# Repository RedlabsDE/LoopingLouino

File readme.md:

# LoopingLouino Project

find pictures and further description here: https://redlabs.de/blog/looping-louino/

## Repository Overview
- **documentation**
  - pictures of this project
- **firmware**
  - Arduino Project
- **hardware**
  - **KiCAD** Project Folder including schematic, PCB layout and BOM
  - **schematic** and fabrication layer drawing as PDF
  - **datasheet** of used components
  
## Hardware
- Order PCB: https://aisler.net/p/MKIYMUSK
- Assemble PCB (find BOM in \hardware\schematic)
- Rework PCB as described in the schematic

## Firmware

### Flash Arduino bootloader to your Atmega328

1. Open Atmel Studio (now Microchip Studio)
2. Start the Tool Manager. Connec your Atmel ISP to your PC and to the PCB (CON2, ISP 6-pin).
3. Select Tool and Device. Apply & Read.
4. "Fuses": Set Fuses (according to picture "Arduino Fuses.pg"). Program fuses to Device.
5. "Memories": For Flash, select the "optiboot_atmega328.hex" file. Program&Verify.

... find pictures and data here: \firmware\Arduino Bootloader

### Upload the LoopingLouino Fimrware 

Prepare:
- Get an USB/UART converter
- Connect the UART to the PCB (Pinheader P1, or use the Audio Jack J1)

Upload:
1. Open the firmware folder in VSCode
2. Install the "PlatformIO IDE" extension
3. Open the folder "180223-094129-pro16MHzatmega328" with the extension
4. Build and Upload the project.

... find other projects: https://redlabs.de/

### Debug the Firmware

In main.cpp set "#define DEBUG 1" to get serial debug information (8n1 19200)

### Adaptions in the Firware

According to the used Supply Voltage, set: #define SPEED_CORRECTION_FACTOR (main.h)

According to the number of LEDs used, set: #define NUM_LEDS (LEDcntrl.h)

## Mechanics

//TODO: add pictures

Open all screws (short / long)

remove black cable (between motor and batteries)
remove red cable (between switch and batteries)
remove battery clips

add new black cable to motor (20cm)
add new red cable to switch (20cm)

cut through plastic (battery holder)
drill through plastic frame (for DC Jack, Button and optional RC-Jack)

cut digital LED strip and attach 3-wire ribbon cable (20LEDs, or other number)

solder 3-wire LED cable to PCB
solder 2-Wire Motor-and-Switch cable to PCB

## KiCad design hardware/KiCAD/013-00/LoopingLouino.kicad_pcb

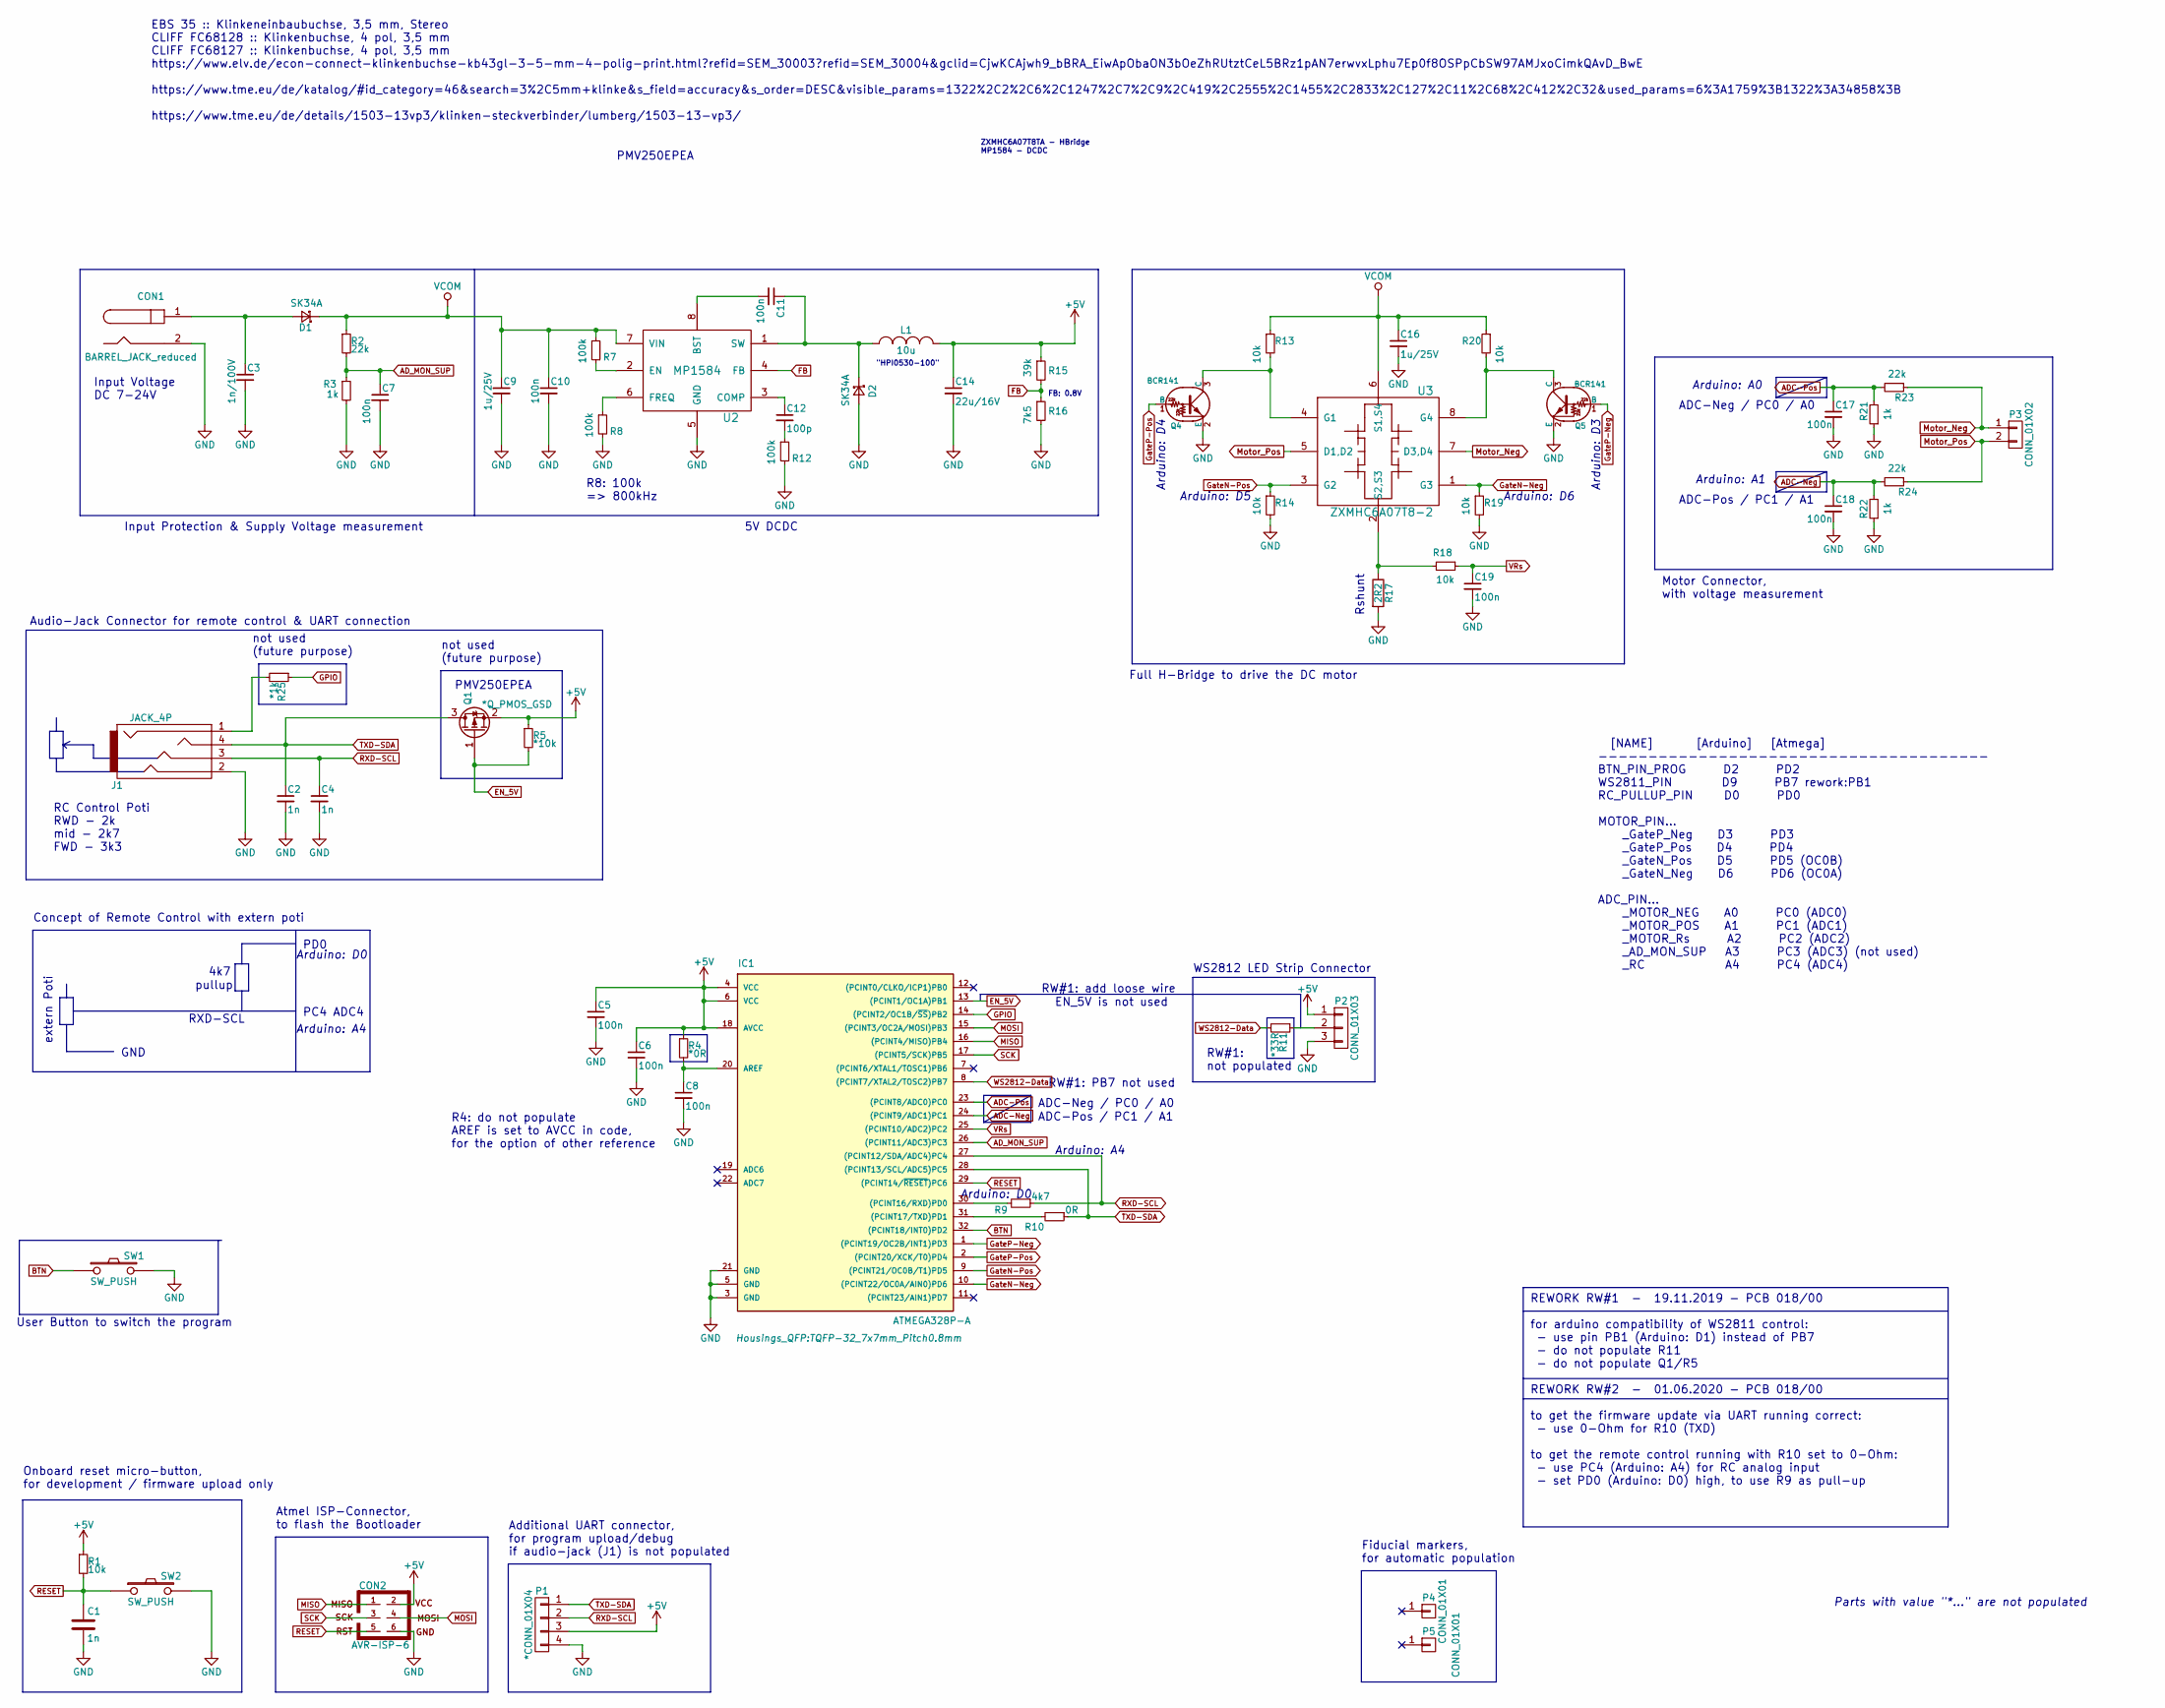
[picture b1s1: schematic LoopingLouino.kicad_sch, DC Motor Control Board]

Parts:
C1, C2, C4: 1n; C_0603
C3: 1n/100V; C_0603
C5, C6, C7, C8, C10, C11, C17, C18, C19: 100n; C_0603
C9, C16: 1u/25V; C_0805
C12: 100p; C_0603
C14: 22u/16V; C_1206
CON1: BARREL_JACK_reduced
CON2: AVR-ISP-6; MicroMatch_2x3_SMD
D1, D2: SK34A; D_SMA
IC1: ATMEGA328P-A; TQFP-32_7x7mm_Pitch0.8mm
J1: JACK_4P; Klinkenbuchse-1503-13VP3
L1: 10u; Inductor_HPI0530-xxx
P1: *CONN_01X04; PIN_ARRAY_4x1_drill_0.8mm
P2: CONN_01X03; PIN_ARRAY_3x1_drill_0.8mm
P3: CONN_01X02; JST_XH2P_oval_pads
P4, P5: CONN_01X01; Fiducial_1mm_Dia_2mm_Outer
Q1: *Q_PMOS_GSD; SOT-23-RL
Q4, Q5: BCR141; SOT-23-RL
R1, R13, R14, R18, R19, R20: 10k; R_0603
R2, R23, R24: 22k; R_0603
R3, R21, R22: 1k; R_0603
R4: *0R; R_0603
R5: *10k; R_0603
R7, R8, R12: 100k; R_0603
R9: 4k7; R_0603
R10: 0R; R_0603
R11: *33R; R_0603
R15: 39k; R_0603
R16: 7k5; R_0603
R17: 2R2; R_0805_redlabs
R25: *1k; R_0603
SW1: SW_PUSH; SW_Tactile_SPST_Angled_PTS645Vx83-2LFS
SW2: SW_PUSH; SMD_pushbutton_4x6mm
U2: MP1584; SO8N-RL
U3: ZXMHC6A07T8-2; SOT-223-8

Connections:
+5V: C5.1, C6.1, C14.1, CON2.2, IC1.4 (VCC), IC1.6 (VCC), IC1.18 (AVCC), L1.2, P1.3, P2.1, Q1.2 (S), R1.1, R4.1, R5.1, R15.1
ADC-Neg: C18.1, IC1.24 ((PCINT9/ADC1)PC1), R22.2, R24.2
ADC-Pos: C17.1, IC1.23 ((PCINT8/ADC0)PC0), R21.2, R23.2
AD_MON_SUP: C7.1, IC1.26 ((PCINT11/ADC3)PC3), R2.2, R3.1
BTN: IC1.32 ((PCINT18/INT0)PD2), SW1.1
EN_5V: IC1.13 ((PCINT1/OC1A)PB1), Q1.1 (G), R5.2
FB: R15.2, R16.1, U2.4 (FB)
GND: C1.2, C2.2, C3.2, C4.2, C5.2, C6.2, C7.2, C8.2, C9.2, C10.2, C14.2, C16.2, C17.2, C18.2, C19.2, CON1.2, CON2.6, D2.2 (A), IC1.3 (GND), IC1.5 (GND), IC1.21 (GND), J1.2, P1.4, P2.3, Q4.2 (E), Q5.2 (E), R3.2, R8.2, R12.2, R14.2, R16.2, R17.2, R19.2, R21.1, R22.1, SW1.2, SW2.2, U2.5 (GND)
GPIO: IC1.14 ((PCINT2/OC1B/~SS)PB2), R25.1
GateN-Neg: IC1.10 ((PCINT22/OC0A/AIN0)PD6), R19.1, U3.1 (G3)
GateN-Pos: IC1.9 ((PCINT21/OC0B/T1)PD5), R14.1, U3.3 (G2)
GateP-Neg: IC1.1 ((PCINT19/OC2B/INT1)PD3), Q5.1 (B)
GateP-Pos: IC1.2 ((PCINT20/XCK/T0)PD4), Q4.1 (B)
MISO: CON2.1, IC1.16 ((PCINT4/MISO)PB4)
MOSI: CON2.4, IC1.15 ((PCINT3/OC2A/MOSI)PB3)
Motor_Neg: P3.1, R23.1, U3.7 (D3,D4)
Motor_Pos: P3.2, R24.1, U3.5 (D1,D2)
unnamed: C3.1, CON1.1, D1.2 (A)
unnamed: C8.1, IC1.20 (AREF), R4.2
unnamed: C11.1, D2.1 (K), L1.1, U2.1 (SW)
unnamed: C11.2, U2.8 (BST)
unnamed: C12.1, U2.3 (COMP)
unnamed: C12.2, R12.1
unnamed: IC1.30 ((PCINT16/RXD)PD0), R9.2
unnamed: IC1.31 ((PCINT17/TXD)PD1), R10.2
unnamed: J1.1, R25.2
unnamed: P2.2, R11.1
unnamed: Q4.3 (C), R13.2, U3.4 (G1)
unnamed: Q5.3 (C), R20.2, U3.8 (G4)
unnamed: R7.2, U2.2 (EN)
unnamed: R8.1, U2.6 (FREQ)
unnamed: R17.1, R18.2, U3.2 (S2,S3)
RESET: C1.1, CON2.5, IC1.29 ((PCINT14/~RESET)PC6), R1.2, SW2.1
RXD-SCL: C4.1, IC1.27 ((PCINT12/SDA/ADC4)PC4), J1.3, P1.2, R9.1
SCK: CON2.3, IC1.17 ((PCINT5/SCK)PB5)
TXD-SDA: C2.1, IC1.28 ((PCINT13/SCL/ADC5)PC5), J1.4, P1.1, Q1.3 (D), R10.1
VCOM: C9.1, C10.1, C16.1, D1.1 (K), R2.1, R7.1, R13.1, R20.1, U2.7 (VIN), U3.6 (S1,S4)
VRs: C19.1, IC1.25 ((PCINT10/ADC2)PC2), R18.1
WS2812-Data: IC1.8 ((PCINT7/XTAL2/TOSC2)PB7), R11.2

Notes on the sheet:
PMV250EPEA
Arduino: D6
ADC-Pos / PC1 / A1
ADC-Neg / PC0 / A0
R4: do not populate AREF is set to AVCC in code, for the option of other reference
Motor Connector, with voltage measurement
Parts with value "*..." are not populated
Arduino: D4
GND
Arduino: D0
Additional UART connector, for program upload/debug if audio-jack (J1) is not populated
"HPI0530-100"
RW#1: PB7 not used
User Button to switch the program
Rshunt
Onboard reset micro-button, for development / firmware upload only
Input Protection & Supply Voltage measurement
Atmel ISP-Connector, to flash the Bootloader
FB: 0.8V
REWORK RW#1 - 19.11.2019 - PCB 018/00 for arduino compatibility of WS2811 control: - use pin PB1 (Arduino: D1) instead of PB7 - do not populate R11 - do not populate Q1/R5 REWORK RW#2 - 01.06.2020 - PCB 018/00 to get the firmware update via UART running correct: - use 0-Ohm for R10 (TXD) to get the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
WS2812 LED Strip Connector
pullup
Arduino: A4
RC Control Poti RWD - 2k mid - 2k7 FWD - 3k3
EBS 35 :: Klinkeneinbaubuchse, 3,5 mm, Stereo CLIFF FC68128 :: Klinkenbuchse, 4 pol, 3,5 mm CLIFF FC68127 :: Klinkenbuchse, 4 pol, 3,5 mm https://www.elv.de/econ-connect-klinkenbuchse-kb43gl-3-5-mm-4-polig-print.html?refid=SEM_30003?refid=SEM_30004&gclid=CjwKCAjwh9_bBRA_EiwApObaON3bOeZhRUtztCeL5BRz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
not used (future purpose)
4k7
RW#1: not populated
Audio-Jack Connector for remote control & UART connection
RXD-SCL
[NAME] [Arduino] [Atmega] --------------------------------------- BTN_PIN_PROG D2 PD2 WS2811_PIN D9 PB7 rework:PB1 RC_PULLUP_PIN D0 PD0 MOTOR_PIN... _GateP_Neg D3 PD3 _GateP_Pos D4 PD4 _GateN_Pos D5 PD5 (OC0B) _GateN_Neg D6 PD6 (OC0A) ADC_PIN... _MOTOR_NEG A0 PC0 (ADC0) _MOTOR_POS A1 PC1 (ADC1) _MO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
EN_5V is not used
Arduino: D3
Arduino: D5
R8: 100k => 800kHz
Arduino: A0
Full H-Bridge to drive the DC motor
extern Poti
RW#1: add loose wire
Fiducial markers, for automatic population

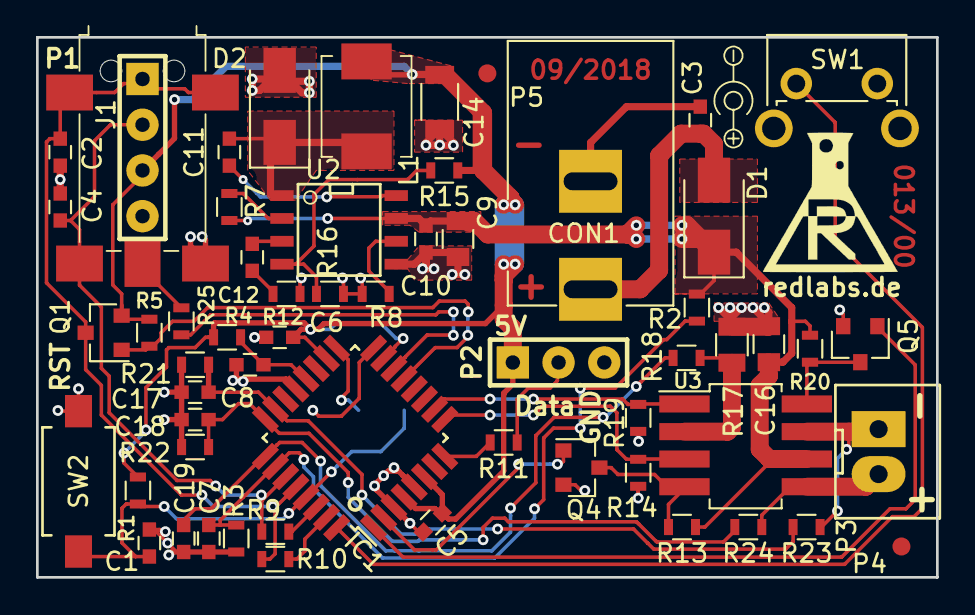
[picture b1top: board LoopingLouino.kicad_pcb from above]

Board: 2 copper layers, 50.0 x 30.0 mm, 60 parts (1 on the bottom side), 39 nets.

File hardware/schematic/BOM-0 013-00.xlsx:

redlabs.de | BOM 013/00 | LoopingLouino
 |  | Total parts: | 50
v C | 22u | C_1206 | 1
C14 | 22u
v C | 100p | C_0603 | 1
C12 | 100p
v C | 1n | C_0603 | 4
C1 | 1n
C2 | 1n
C3 | 1n/200V
C4 | 1n
v C | 100n | C_0603 | 9
C5 | 100n
C6 | 100n
C7 | 100n
C8 | 100n
C10 | 100n/25V
C11 | 100n
C17 | 100n
C18 | 100n
C19 | 100n
v C | 1u/25V | C_0805 | 2
C9 | 1u/25V
C16 | 1u/25V
v R | 2R2 | R_0805 | 1
R17 | 2R2
v R | 0R | R_0603 | 1
R10 | 0R
v R | 1k | R_0603 | 3
R3 | 1k
R21 | 1k
R22 | 1k
v R | 4k7 | R_0603 | 1
R9 | 4k7
v R | 7k5 | R_0603 | 1
R16 | 7k5
v R | 10k | R_0603 | 6
R1 | 10k
R13 | 10k
R14 | 10k
R18 | 10k
R19 | 10k
R20 | 10k
v R | 22k | R_0603 | 3
R2 | 22k
R23 | 22k
R24 | 22k
v R | 39k | R_0603 | 1
R15 | 39k
v R | 100k | R_0603 | 3
R7 | 100k
R8 | 100k
R12 | 100k
v D | SK34A | D_SMA | 2
D1 | SK34A
D2 | SK34A
v L | 10uH | D_SMA | 1
L1 | 10uH (HPI0530-100)
v Q | BCR141 | SOT-23 | 2
Q4 | BCR141
Q5 | BCR141
v IC |  |  | 3
IC1 | ATMEGA328P-A | TQFP-32_7x7mm_Pitch0.8mm
U2 | MP1584 | SO8N
U3 | ZXMHC6A07T8-2 | SOT-223-8
v SW | Switches |  | 2
SW1 | SW_PUSH | SW_Tactile_SPST_Angled_PTS645Vx83-2LFS
SW2 | SW_PUSH | SMD_pushbutton_4x6mm
v CON | Connectors |  | 3
J1 | JACK_4P | Klinkenbuchse-1503-13VP3
CON1 | BARREL_JACK_reduced | BARREL_JACK_reduced
CON2 | AVR-ISP-6 | MicroMatch_2x3_SMD
v P | Pin Array
P2 | CONN_01X03 | PIN_ARRAY_3x1_drill_0.8mm
P3 | CONN_01X02 | JST_XH2P_oval_pads
v P | Not Populated |  | 5
R11 | 33R | R_0603
R4 | 0R | R_0603
R5 | 10k | R_0603
R25 | 1k | R_0603
Q1 | PMV250 | SOT-23

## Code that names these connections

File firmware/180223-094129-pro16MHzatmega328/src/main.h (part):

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//Arduino Mini Pro
//5V, 16MHz quarz
//Onboard 5V/150mA LDO
//Pin 13 (PB5) Onboard green LED (active high)
*/

/* PCB 013/00
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
  [NAME]       [Arduino]   [Atmega]
---------------------------------------
BTN_PIN_PROG      D2      PD2
WS2811_PIN        D9      PB7 rework:PB1
RC_PULLUP_PIN     D0      PD0

MOTOR_PIN...
    _GateP_Neg    D3      PD3
    _GateP_Pos    D4      PD4
    _GateN_Pos    D5      PD5 (OC0B)
    _GateN_Neg    D6      PD6 (OC0A)

ADC_PIN...
    _MOTOR_NEG    A0      PC0 (ADC0)
    _MOTOR_POS    A1      PC1 (ADC1)
    _MOTOR_Rs     A2      PC2 (ADC2)
    _AD_MON_SUP   A3      PC3 (ADC3) (not used)
    _RC           A4      PC4 (ADC4)

*/

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#define BTN_PIN_PROG  2  //switch program

//onboard pullup for RC control
//#define RC_PULLUP_PIN 1  //PD1 GPIO1
#define RC_PULLUP_PIN 0 //REWORK 09-06-2020: use RXD pin to control pull-up

//  Motor control:
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  #define MOTOR_PIN_DIR1  12   //
  #define MOTOR_PIN_DIR2  11  //

  #define MOTOR_PIN_GateP_Neg   3 //PD3
  #define MOTOR_PIN_GateP_Pos   4 //PD4
  #define MOTOR_PIN_GateN_Pos   5 //PD5 PWM (OC0B)
  #define MOTOR_PIN_GateN_Neg   6 //PD6 PWM (OC0A)

  #define ADC_PIN_MOTOR_POS 1
  #define ADC_PIN_MOTOR_NEG 0
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
//  analog inputs:
//Motor current sense
#define ADC_PIN_MOTOR_Rs 2 //PC2 ADC2

//Remote Control
//#define ADC_PIN_RC  5     //PC5 ADC5
#define ADC_PIN_RC  4     //PC4 ADC4 RXD //REWORK 09-06-2020:

//Supply voltage measurement
#define ADC_PIN_MON_SUP  3     //PC3 ADC3


///////////////////////////////////////////////////////////////////////////////
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//RC control (extern variable resistor to GND)
//Schematic: (PIN-OUT-5V)---|4k7|---(ADC)---|poti|---(GND)

// voltage measured at PC5 in mV (black RC Felix&Nadja) 013/00 (4k7 onboard pullup)
// 5V supply: 4700
// ADC_max =  1810  (full speed forward + full fine regulator forward)
// ADC_norm = 1650 (speed regulator medium forward + fine regulator in mid position)
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// int ADC_low =   231;


// voltage measured at PC4 in mV (blue RC) 013/00 (4k7 onboard pullup)
// 5V supply: 5100
// ADC_max =  2027  (full speed forward + full fine regulator forward)
// ADC_norm = 1967 (speed regulator medium forward + fine regulator in mid position)
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
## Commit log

2020-06-17 init
2020-06-17 Init upload - R1.9 from dropbox
2022-10-27 setup project structure
2025-03-12 add new KiCAD files
    add information on how to flash the bootloader
2025-03-14 use 20 LEDs
